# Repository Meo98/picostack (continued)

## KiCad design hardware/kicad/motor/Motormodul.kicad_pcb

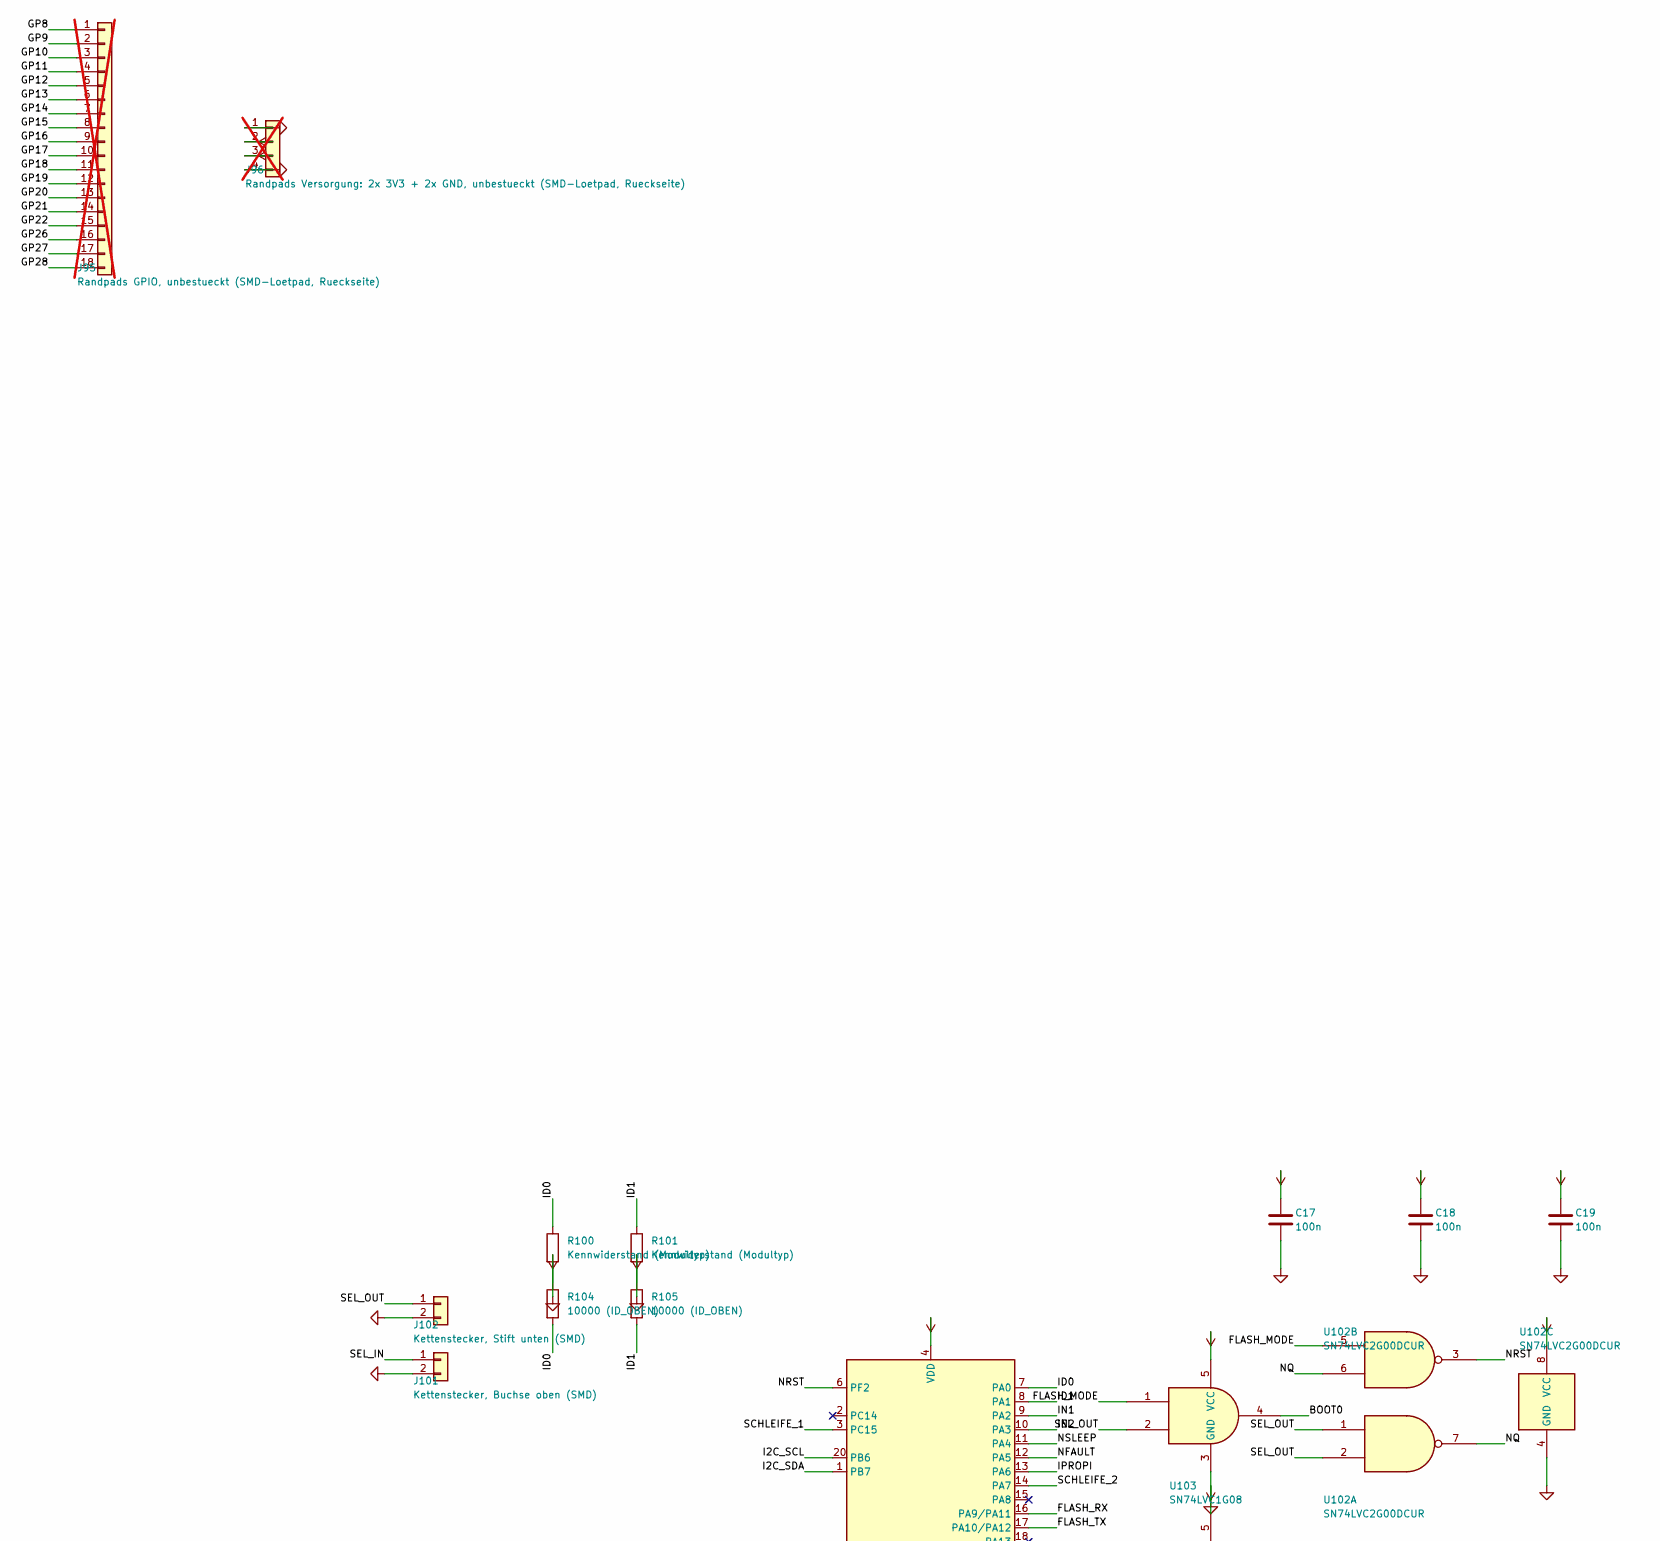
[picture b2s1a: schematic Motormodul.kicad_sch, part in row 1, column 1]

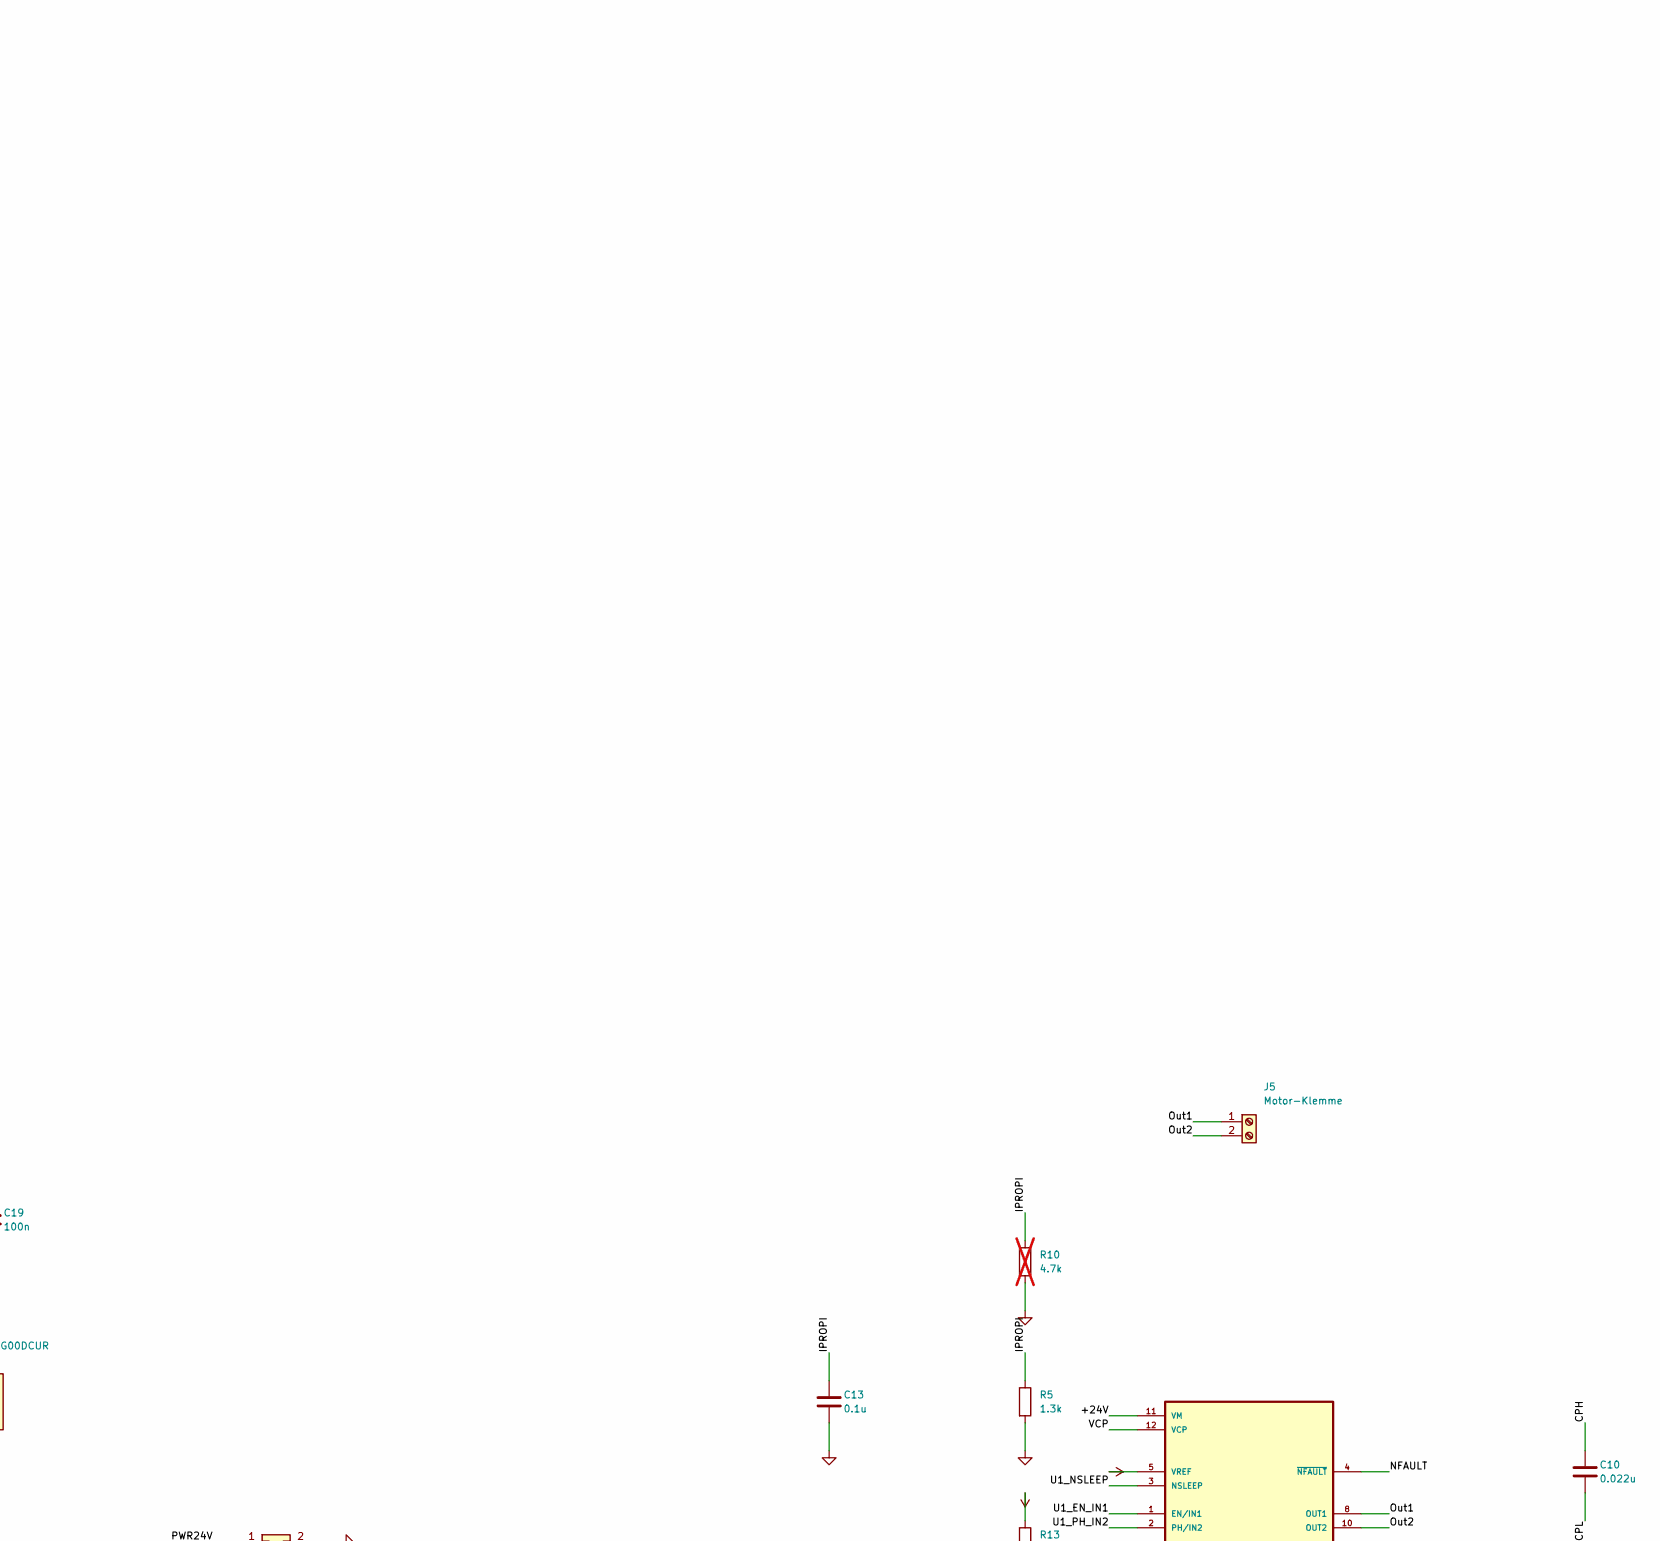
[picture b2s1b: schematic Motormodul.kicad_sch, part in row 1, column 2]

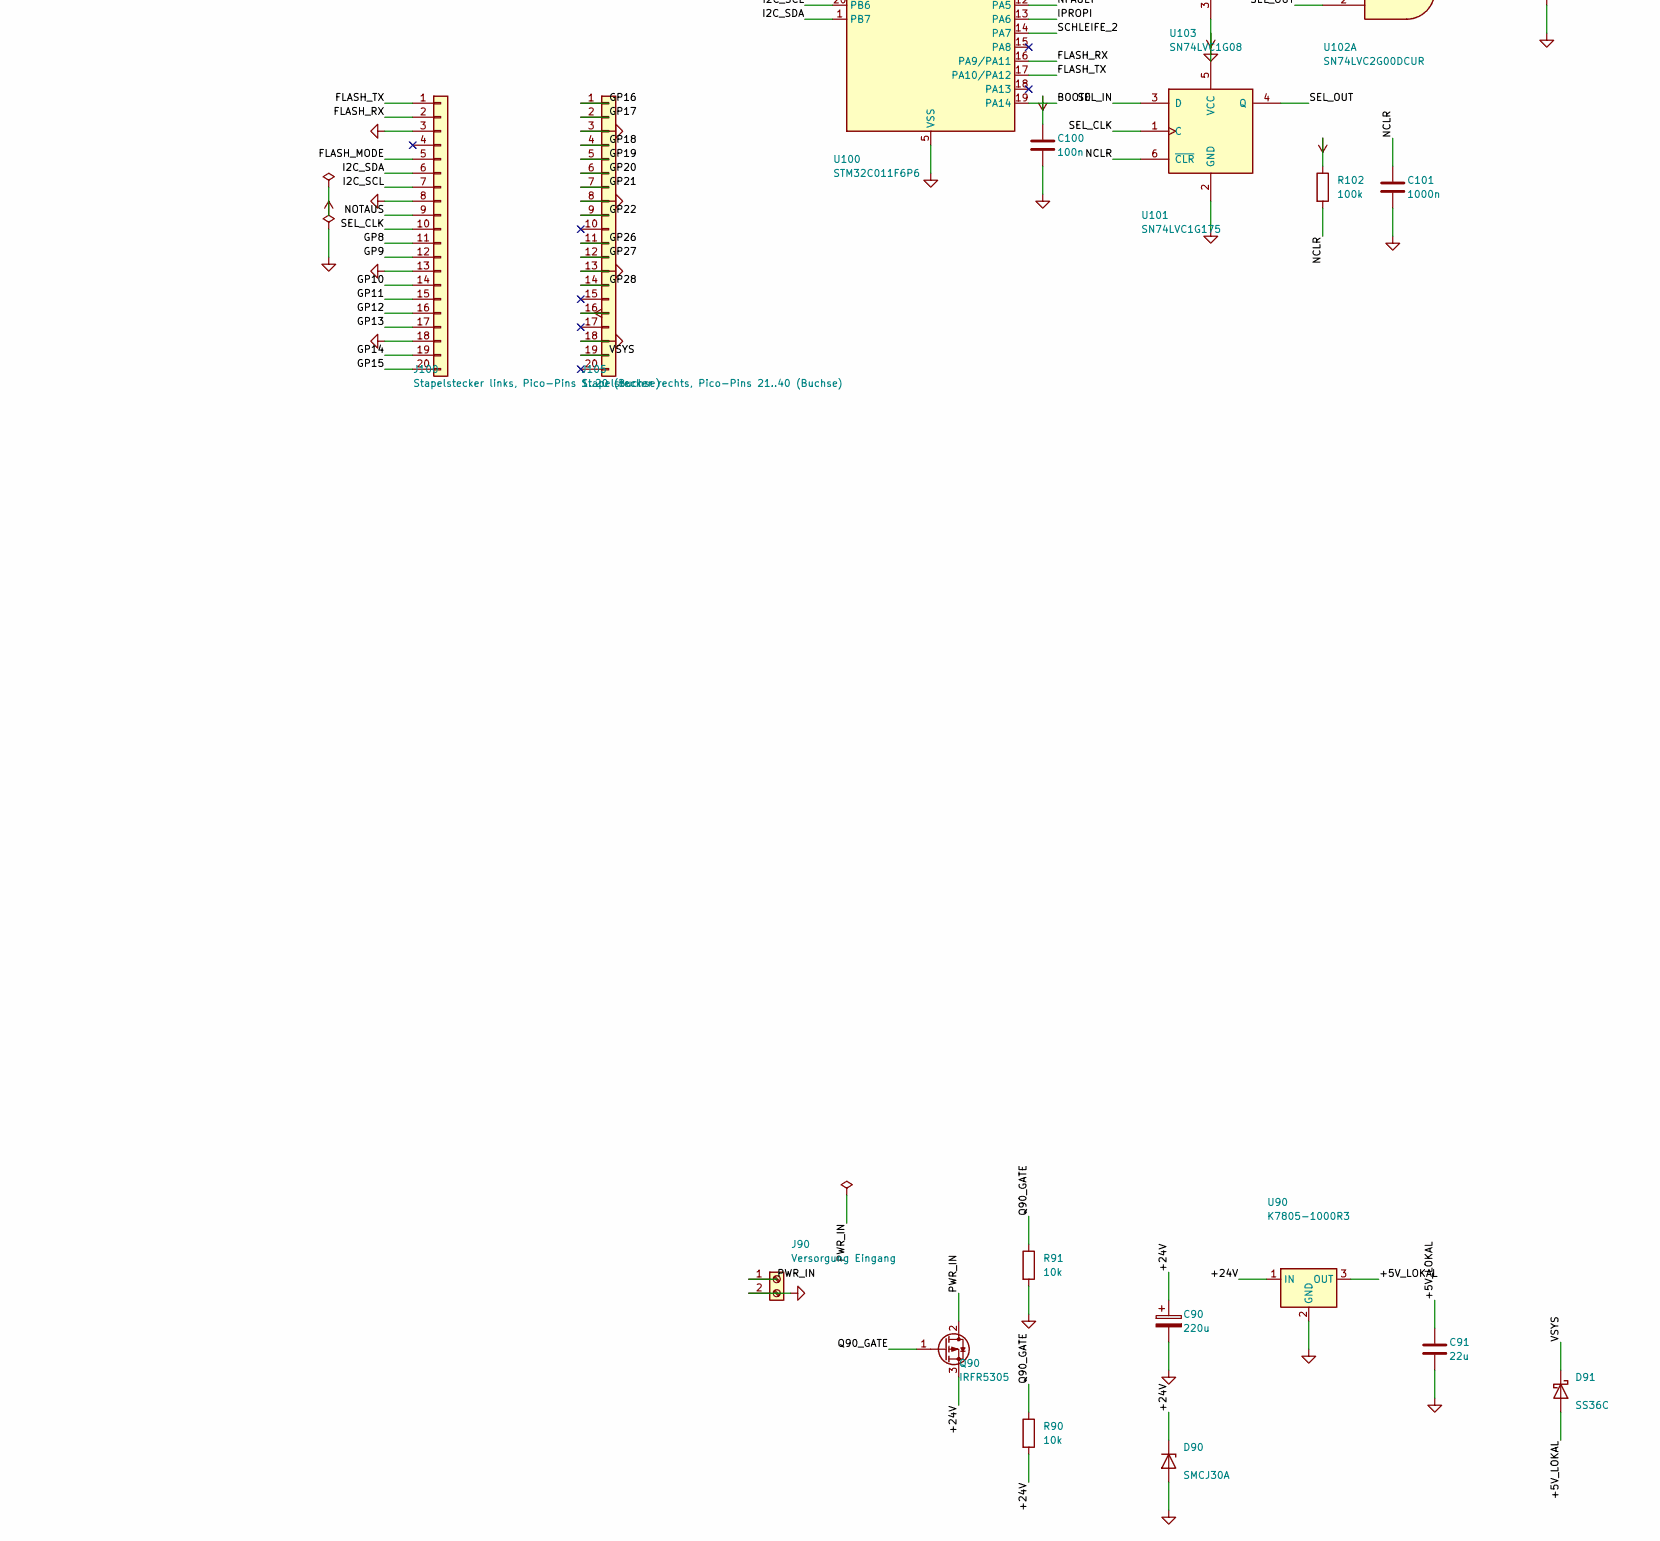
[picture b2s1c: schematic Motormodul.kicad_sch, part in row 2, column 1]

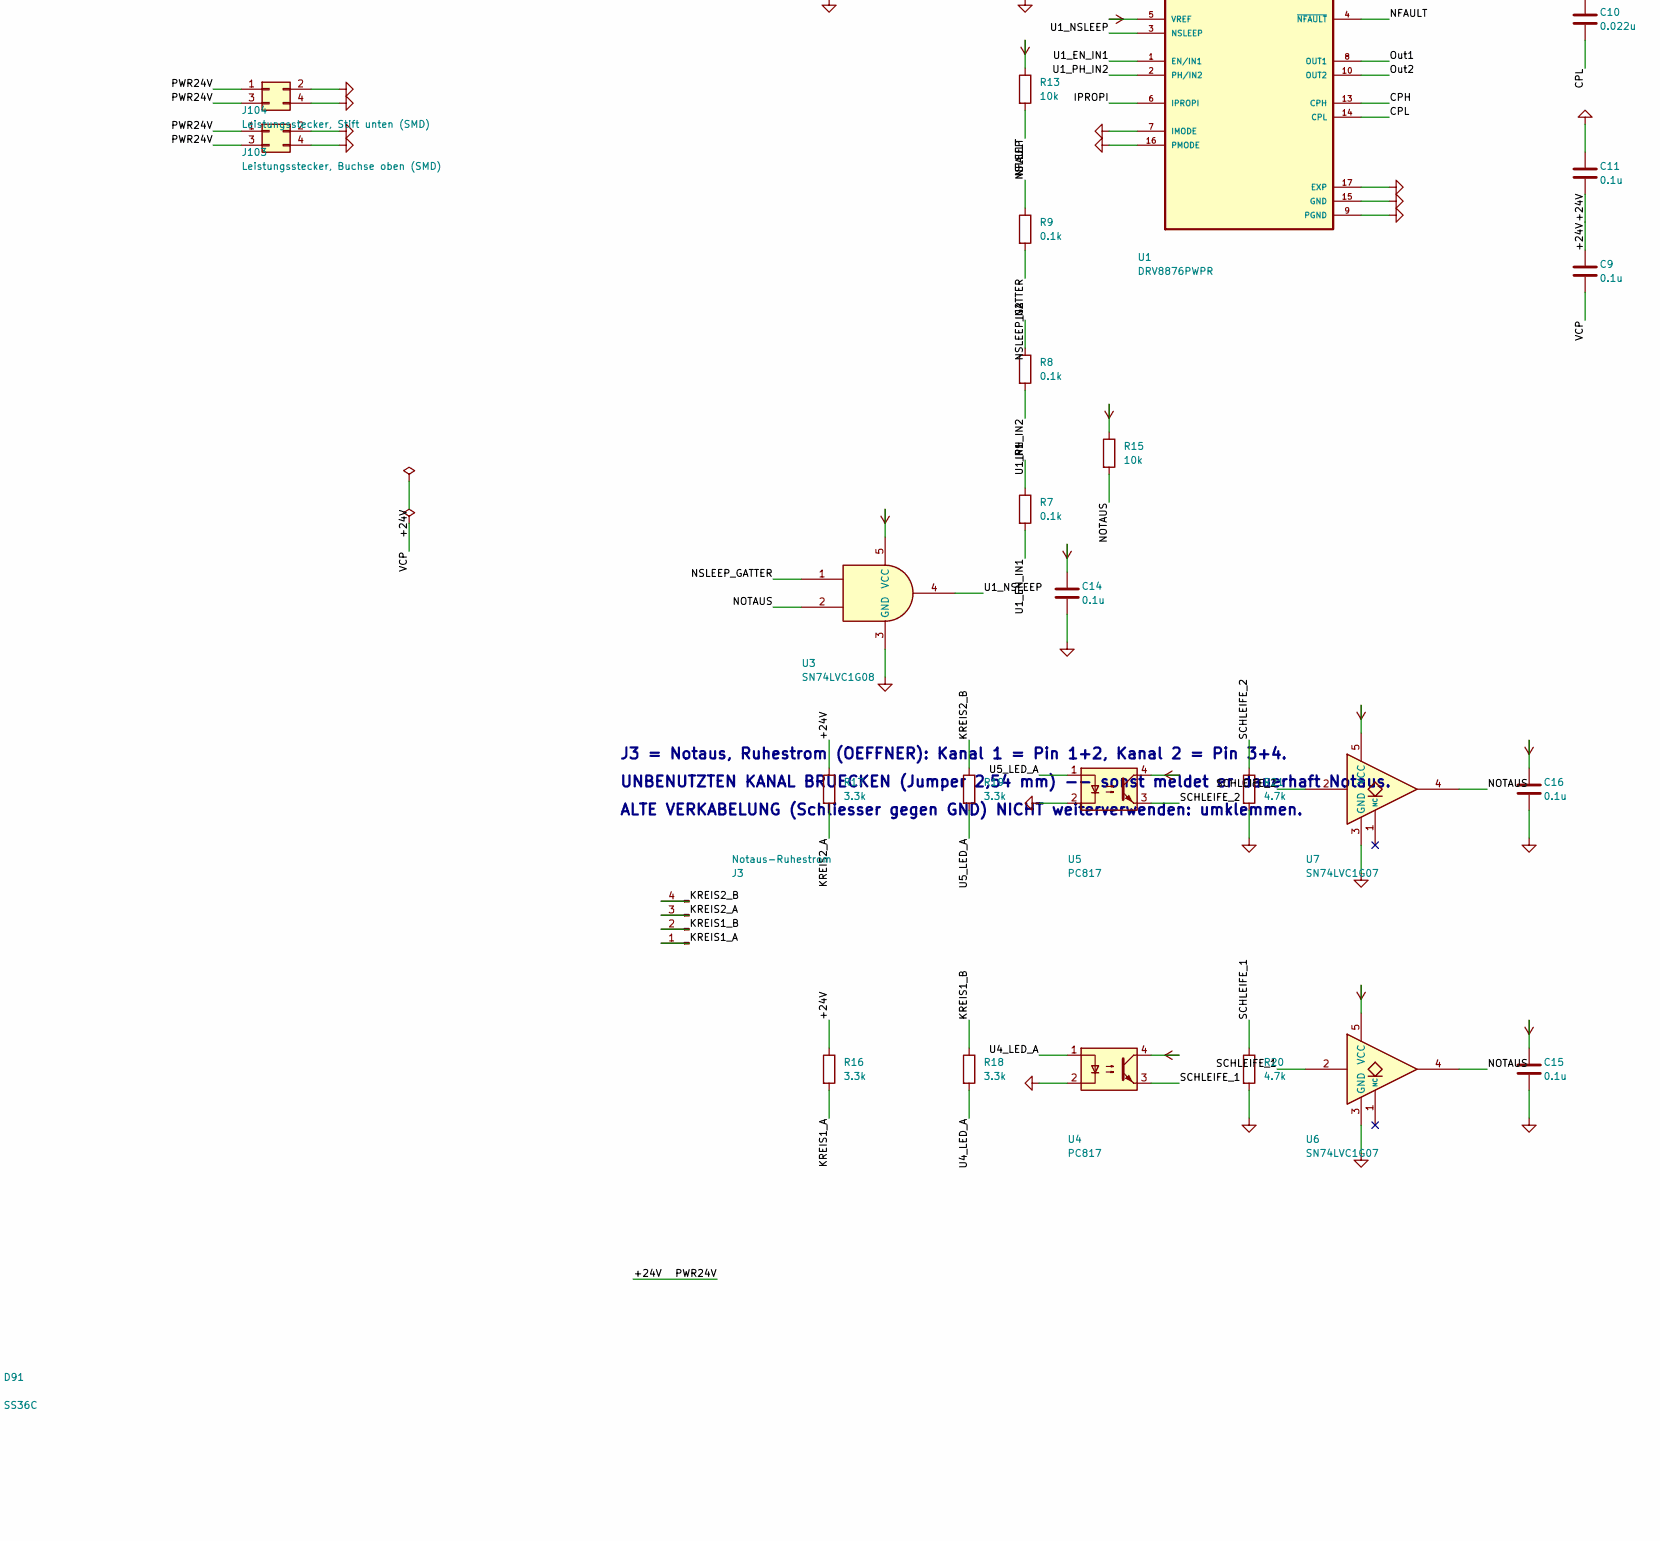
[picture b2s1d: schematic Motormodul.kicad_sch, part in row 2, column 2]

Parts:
C9, C11, C13, C14, C15, C16: 0.1u; C_0805_2012Metric_Pad1.18x1.45mm_HandSolder
C10: 0.022u; C_0805_2012Metric_Pad1.18x1.45mm_HandSolder
C17, C18, C19: 100n; C_0805_2012Metric_Pad1.18x1.45mm_HandSolder; LCSC C49678
C90: 220u; CP_Radial_D8.0mm_P3.50mm
C91: 22u; C_0805_2012Metric_Pad1.18x1.45mm_HandSolder
C100: 100n; C_0805_2012Metric_Pad1.18x1.45mm_HandSolder
C101: 1000n; C_0805_2012Metric_Pad1.18x1.45mm_HandSolder
D90: SMCJ30A; D_SMC
D91: SS36C; D_SMC
J3: Notaus-Ruhestrom; PinHeader_1x04_P2.54mm_Vertical
J5: Motor-Klemme; TerminalBlock_Phoenix_MKDS-3-2-5.08_1x02_P5.08mm_Horizontal
J90: Versorgung Eingang; TerminalBlock_Phoenix_PT-1,5-2-3.5-H_1x02_P3.50mm_Horizontal
J95: Randpads GPIO, unbestueckt (SMD-Loetpad, Ruecksei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; Randpad_Reihe_1x18; not fitted
J96: Randpads Versorgung: 2x 3V3 + 2x GND, unbestueckt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; Randpad_Reihe_1x04; not fitted
J100: Stapelstecker links, Pico-Pins 1..20 (Buchse); PinSocket_1x20_P2.54mm_Vertical
J101: Kettenstecker, Buchse oben (SMD); PinSocket_1x02_P2.54mm_Vertical_SMD_Pin1Left
J102: Kettenstecker, Stift unten (SMD); PinHeader_1x02_P2.54mm_Vertical_SMD_Pin1Left
J103: Leistungsstecker, Buchse oben (SMD); PinSocket_2x02_P2.54mm_Vertical_SMD
J104: Leistungsstecker, Stift unten (SMD); PinHeader_2x02_P2.54mm_Vertical_SMD
J105: Stapelstecker rechts, Pico-Pins 21..40 (Buchse); PinSocket_1x20_P2.54mm_Vertical
Q90: IRFR5305; TO-252-3_TabPin2
R5: 1.3k; R_0805_2012Metric_Pad1.20x1.40mm_HandSolder
R7, R8, R9: 0.1k; R_0805_2012Metric_Pad1.20x1.40mm_HandSolder
R10: 4.7k; R_0805_2012Metric_Pad1.20x1.40mm_HandSolder; not fitted
R13, R15, R90, R91: 10k; R_0805_2012Metric_Pad1.20x1.40mm_HandSolder
R16, R17, R18, R19: 3.3k; R_1206_3216Metric
R20, R21: 4.7k; R_0805_2012Metric_Pad1.20x1.40mm_HandSolder
R100, R101: Kennwiderstand (Modultyp); R_0805_2012Metric_Pad1.20x1.40mm_HandSolder
R102: 100k; R_0805_2012Metric_Pad1.20x1.40mm_HandSolder
R104, R105: 10000 (ID_OBEN); R_0805_2012Metric_Pad1.20x1.40mm_HandSolder
U1: DRV8876PWPR; IC_DRV8876PWPR
U3, U103: SN74LVC1G08; SOT-353_SC-70-5
U4, U5: PC817; PC817_SMT_Gullwing
U6, U7: SN74LVC1G07; SOT-353_SC-70-5; LCSC C7830
U90: K7805-1000R3; Converter_DCDC_RECOM_R-78B-2.0_THT
U100: STM32C011F6P6; TSSOP-20_4.4x6.5mm_P0.65mm
U101: SN74LVC1G175; SOT-363_SC-70-6
U102: SN74LVC2G00DCUR; VSSOP-8_2.3x2mm_P0.5mm

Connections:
/+5V_LOKAL: C91.1, D91.2 (A), U90.3 (OUT)
/+24V: C9.1, C11.2, C90.1, D90.1 (K), J103.1, J103.3, J104.1, J104.3, Q90.3 (S), R16.1, R17.1, R90.2, U1.11 (VM), U90.1 (IN)
/BOOT0: U100.19 (PA14), U103.4
/CPH: C10.1, U1.13 (CPH)
/CPL: C10.2, U1.14 (CPL)
/FLASH_MODE: J100.5, U102.5, U103.1
/FLASH_RX: J100.2, U100.16 (PA9/PA11)
/FLASH_TX: J100.1, U100.17 (PA10/PA12)
/GP8: J95.1, J100.11
/GP9: J95.2, J100.12
/GP10: J95.3, J100.14
/GP11: J95.4, J100.15
/GP12: J95.5, J100.16
/GP13: J95.6, J100.17
/GP14: J95.7, J100.19
/GP15: J95.8, J100.20
/GP16: J95.9, J105.1
/GP17: J95.10, J105.2
/GP18: J95.11, J105.4
/GP19: J95.12, J105.5
/GP20: J95.13, J105.6
/GP21: J95.14, J105.7
/GP22: J95.15, J105.9
/GP26: J95.16, J105.11
/GP27: J95.17, J105.12
/GP28: J95.18, J105.14
/I2C_SCL: J100.7, U100.20 (PB6)
/I2C_SDA: J100.6, U100.1 (PB7)
/ID0: R100.1, R104.2, U100.7 (PA0)
/ID1: R101.1, R105.2, U100.8 (PA1)
/IN1: R7.1, U100.9 (PA2)
/IN2: R8.1, U100.10 (PA3)
/IPROPI: C13.1, R5.1, R10.1, U1.6 (IPROPI), U100.13 (PA6)
/KREIS1_A: J3.1, R16.2
/KREIS1_B: J3.2, R18.1
/KREIS2_A: J3.3, R17.2
/KREIS2_B: J3.4, R19.1
/NCLR: C101.1, R102.2, U101.6 (~CLR)
/NFAULT: R13.2, U1.4 (~NFAULT), U100.12 (PA5)
/NOTAUS: J100.9, R15.2, U3.2, U6.4, U7.4
/NQ: U102.6, U102.7
/NRST: U100.6 (PF2), U102.3
/NSLEEP: R9.1, U100.11 (PA4)
/NSLEEP_GATTER: R9.2, U3.1
/Out1: J5.1, U1.8 (OUT1)
/Out2: J5.2, U1.10 (OUT2)
/PWR_IN: J90.1, Q90.2 (D)
/Q90_GATE: Q90.1 (G), R90.1, R91.1
/SCHLEIFE_1: R20.1, U4.3, U6.2, U100.3 (PC15)
/SCHLEIFE_2: R21.1, U5.3, U7.2, U100.14 (PA7)
/SEL_CLK: J100.10, U101.1 (C)
/SEL_IN: J101.1, U101.3 (D)
/SEL_OUT: J102.1, U101.4 (Q), U102.1, U102.2, U103.2
/U1_EN_IN1: R7.2, U1.1 (EN/IN1)
/U1_NSLEEP: U1.3 (NSLEEP), U3.4
/U1_PH_IN2: R8.2, U1.2 (PH/IN2)
/U4_LED_A: R18.2, U4.1
/U5_LED_A: R19.2, U5.1
/VCP: C9.2, U1.12 (VCP)
/VSYS: D91.1 (K), J105.19

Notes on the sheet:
J3 = Notaus, Ruhestrom (OEFFNER): Kanal 1 = Pin 1+2, Kanal 2 = Pin 3+4.
UNBENUTZTEN KANAL BRUECKEN (Jumper 2,54 mm) -- sonst meldet er dauerhaft Notaus.
ALTE VERKABELUNG (Schliesser gegen GND) NICHT weiterverwenden: umklemmen.

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
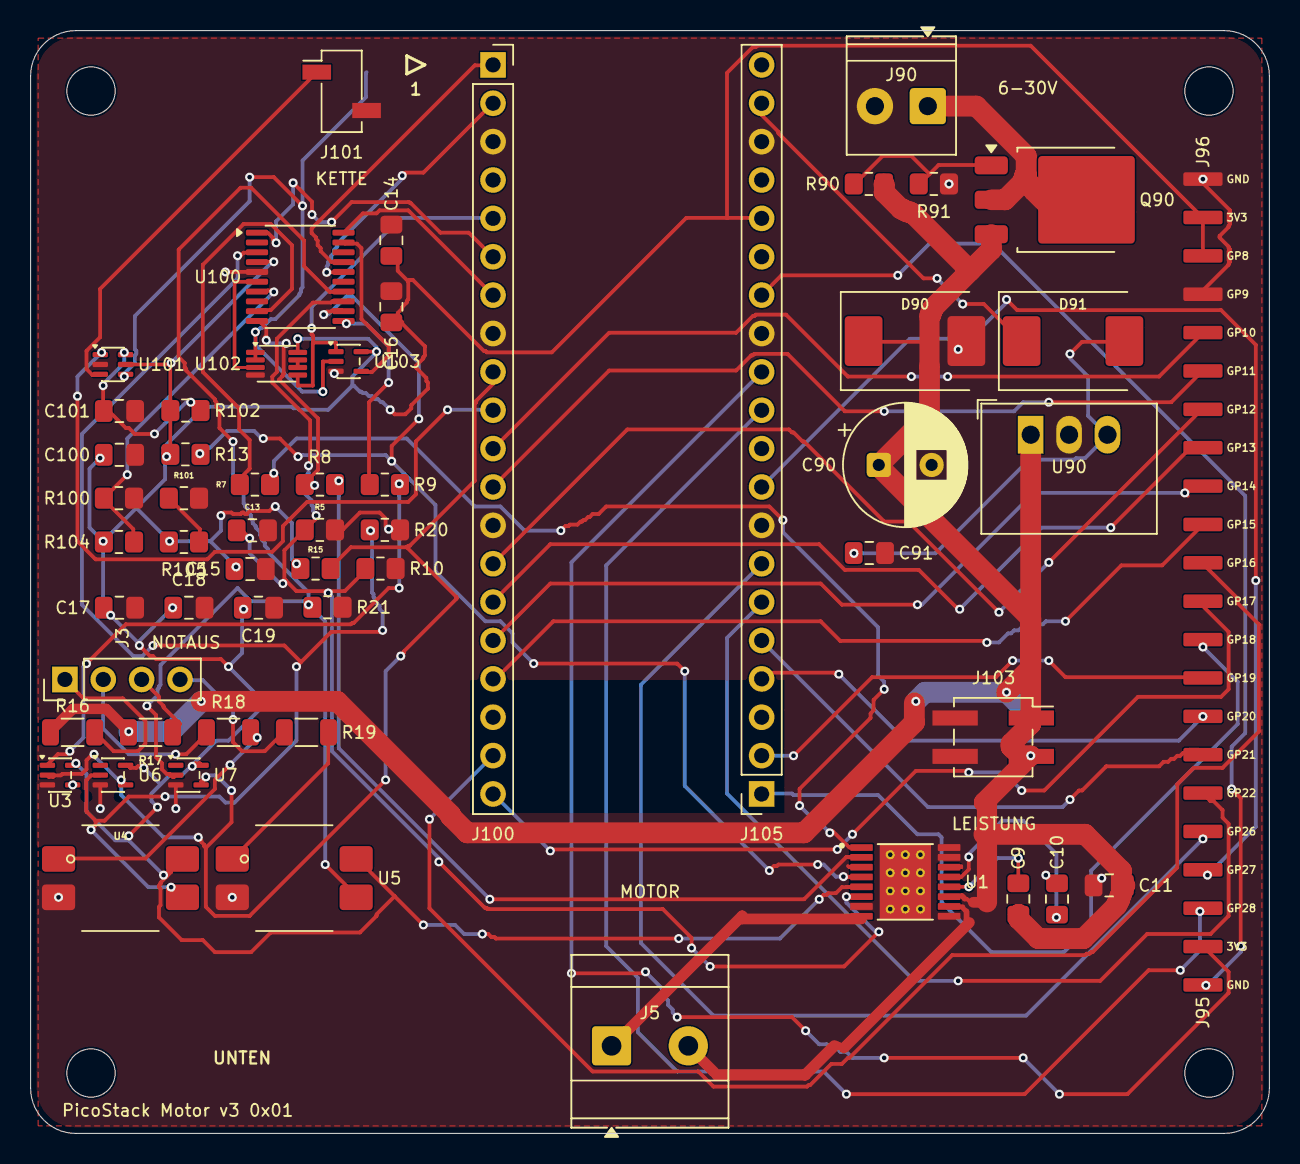
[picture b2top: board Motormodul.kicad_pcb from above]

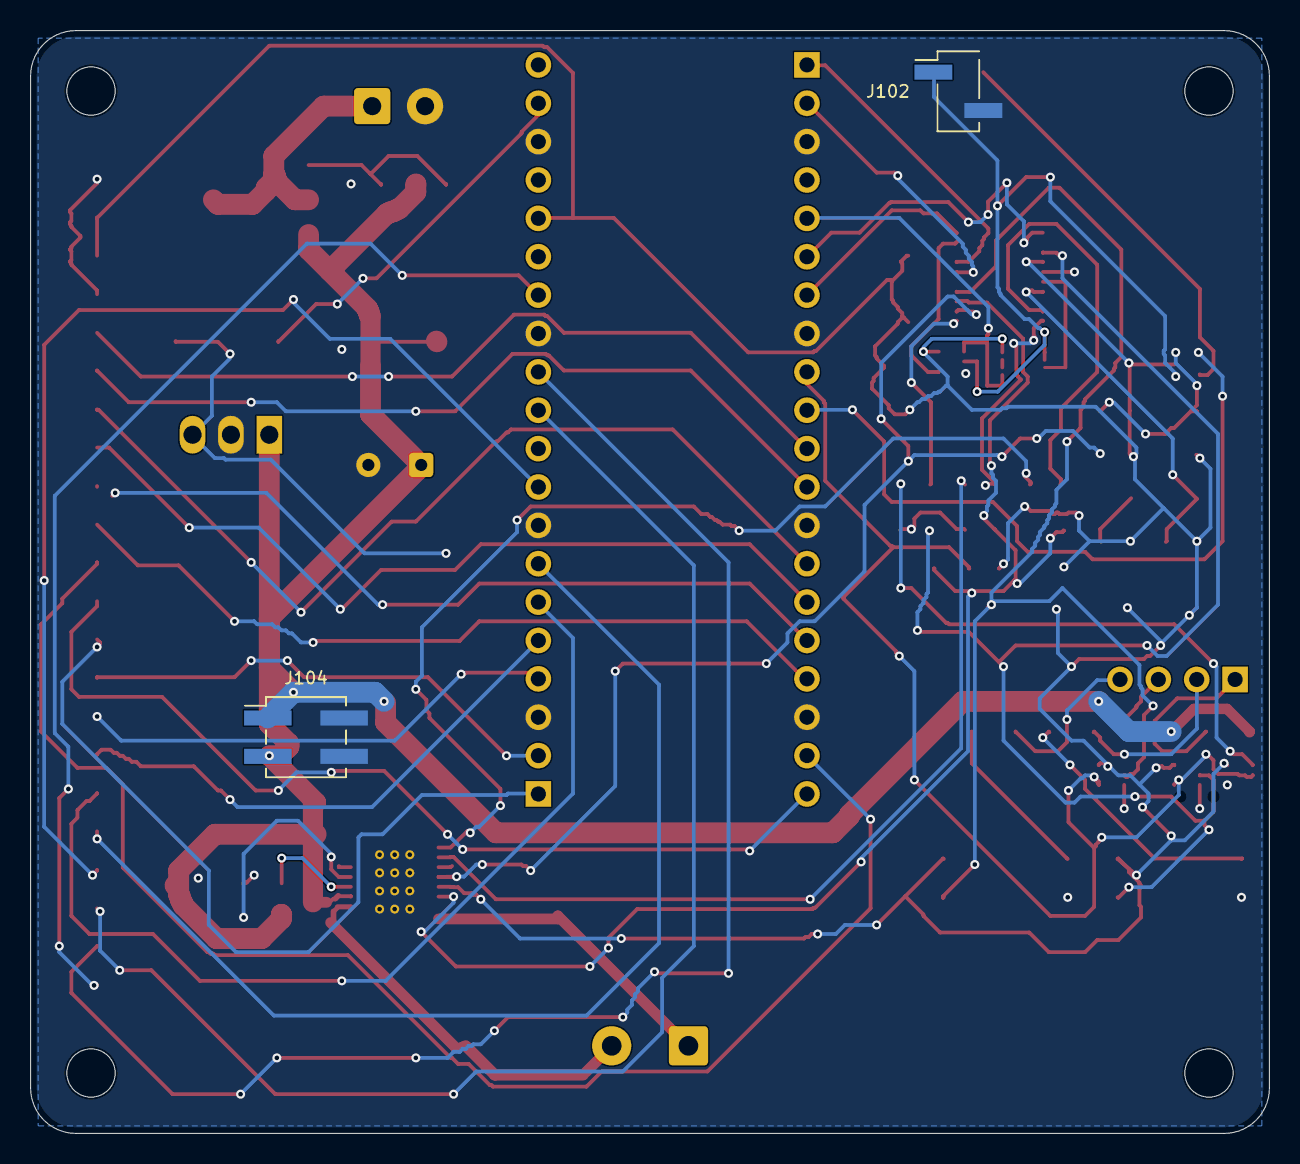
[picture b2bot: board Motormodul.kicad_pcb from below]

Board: 2 copper layers, 82.0 x 73.0 mm, 63 parts (2 on the bottom side), 62 nets.

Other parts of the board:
H1, H2, H3, H4: M3

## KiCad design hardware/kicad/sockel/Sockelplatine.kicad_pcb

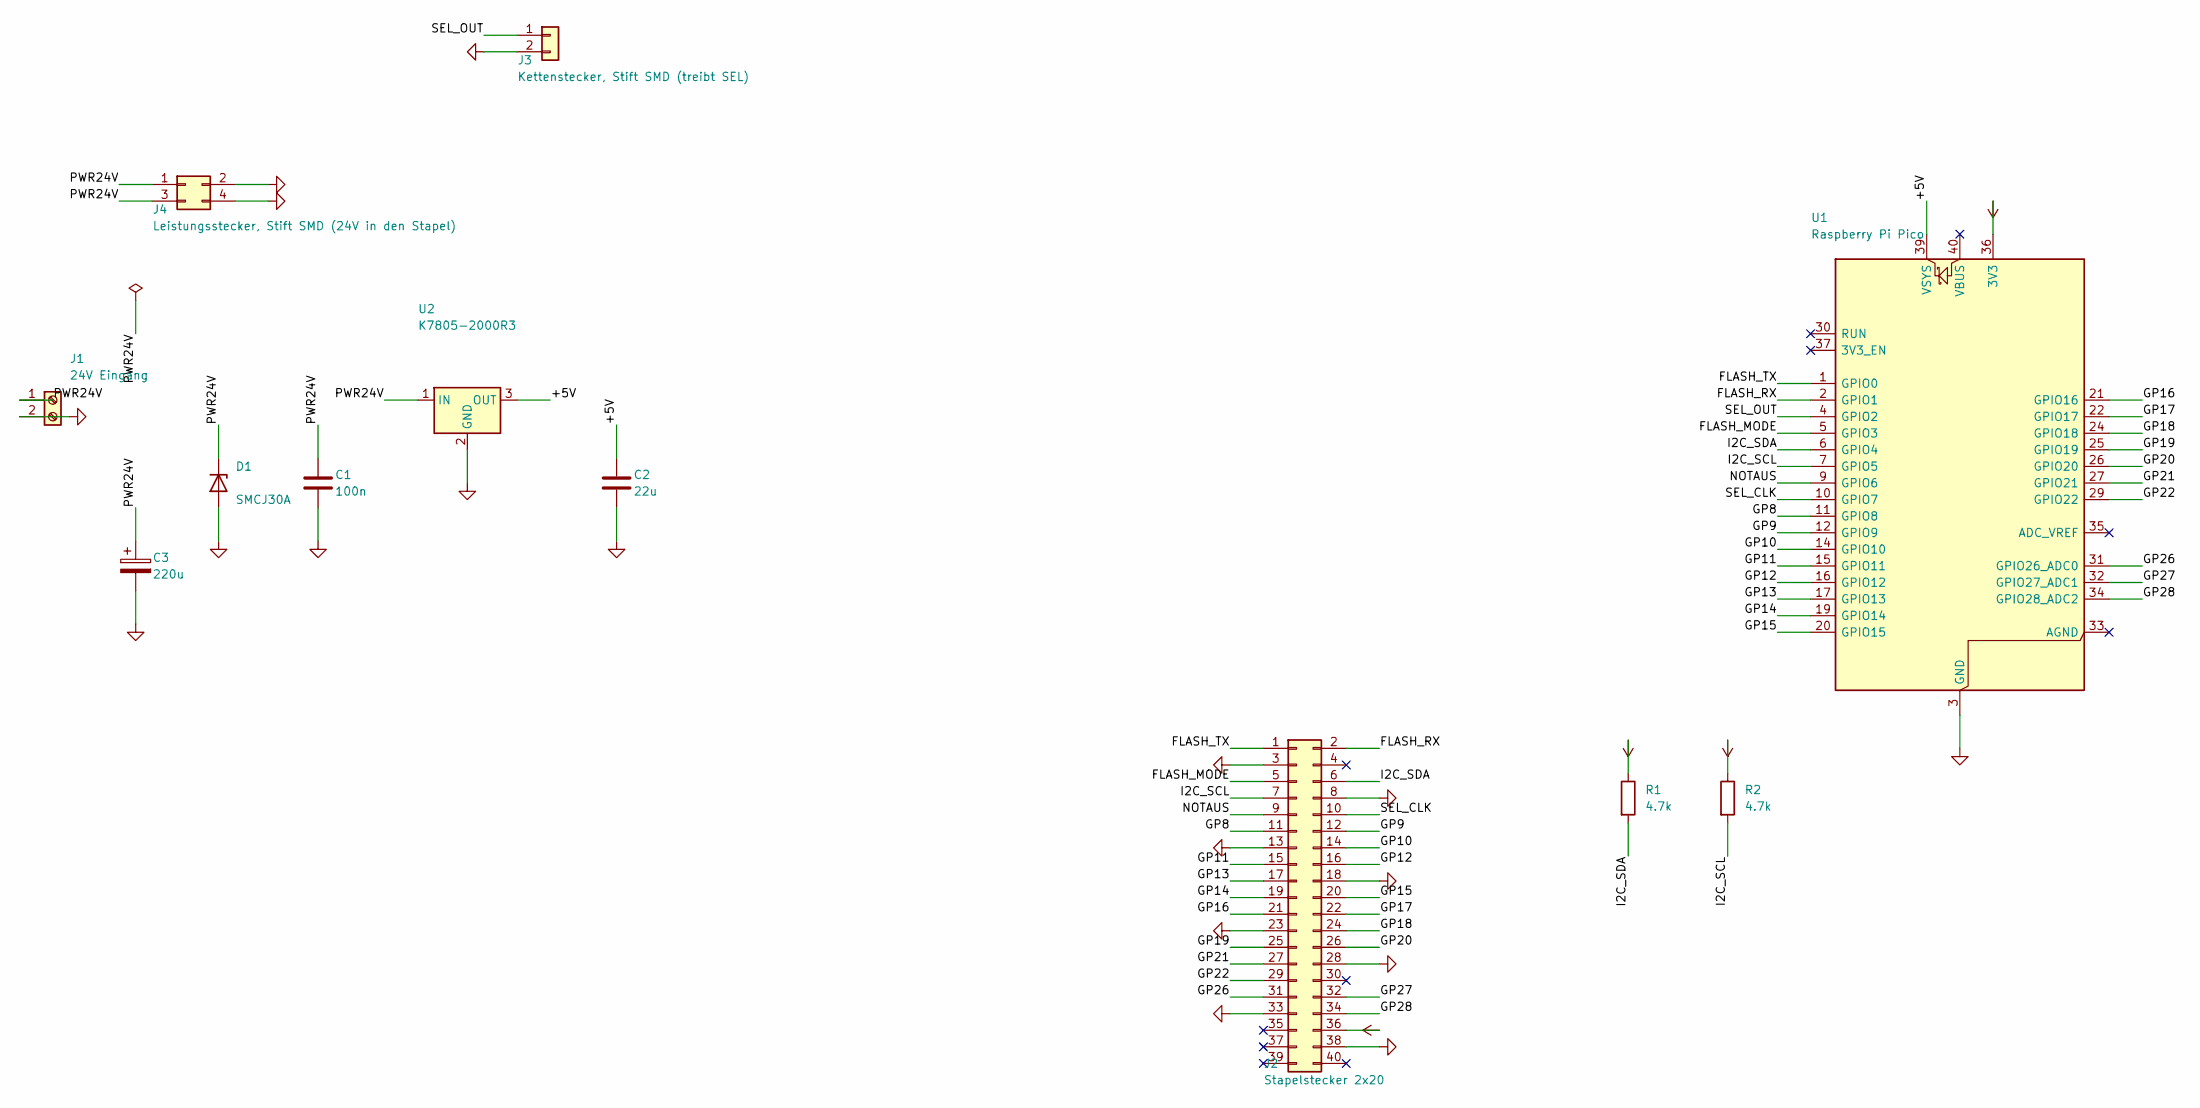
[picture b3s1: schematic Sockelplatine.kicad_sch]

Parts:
C1: 100n; C_0805_2012Metric_Pad1.18x1.45mm_HandSolder
C2: 22u; C_0805_2012Metric_Pad1.18x1.45mm_HandSolder
C3: 220u; CP_Radial_D8.0mm_P3.50mm
D1: SMCJ30A; D_SMC_Handsoldering
J1: 24V Eingang; TerminalBlock_Phoenix_MKDS-3-2-5.08_1x02_P5.08mm_Horizontal
J2: Stapelstecker 2x20; PinHeader_2x20_P2.54mm_Vertical
J3: Kettenstecker, Stift SMD (treibt SEL); PinHeader_1x02_P2.54mm_Vertical_SMD_Pin1Left
J4: Leistungsstecker, Stift SMD (24V in den Stapel); PinHeader_2x02_P2.54mm_Vertical_SMD
R1, R2: 4.7k; R_0805_2012Metric_Pad1.20x1.40mm_HandSolder
U1: Raspberry Pi Pico; RaspberryPi_Pico_Common_THT
U2: K7805-2000R3; Converter_DCDC_RECOM_R-78B-2.0_THT

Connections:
3V3: J2.36, R1.1, R2.1, U1.36 (3V3)
/+5V: C2.1, U1.39 (VSYS), U2.3 (OUT)
/FLASH_MODE: J2.5, U1.5 (GPIO3)
/FLASH_RX: J2.2, U1.2 (GPIO1)
/FLASH_TX: J2.1, U1.1 (GPIO0)
/GP8: J2.11, U1.11 (GPIO8)
/GP9: J2.12, U1.12 (GPIO9)
/GP10: J2.14, U1.14 (GPIO10)
/GP11: J2.15, U1.15 (GPIO11)
/GP12: J2.16, U1.16 (GPIO12)
/GP13: J2.17, U1.17 (GPIO13)
/GP14: J2.19, U1.19 (GPIO14)
/GP15: J2.20, U1.20 (GPIO15)
/GP16: J2.21, U1.21 (GPIO16)
/GP17: J2.22, U1.22 (GPIO17)
/GP18: J2.24, U1.24 (GPIO18)
/GP19: J2.25, U1.25 (GPIO19)
/GP20: J2.26, U1.26 (GPIO20)
/GP21: J2.27, U1.27 (GPIO21)
/GP22: J2.29, U1.29 (GPIO22)
/GP26: J2.31, U1.31 (GPIO26_ADC0)
/GP27: J2.32, U1.32 (GPIO27_ADC1)
/GP28: J2.34, U1.34 (GPIO28_ADC2)
/I2C_SCL: J2.7, R2.2, U1.7 (GPIO5)
/I2C_SDA: J2.6, R1.2, U1.6 (GPIO4)
/NOTAUS: J2.9, U1.9 (GPIO6)
/PWR24V: C1.1, C3.1, D1.1 (K), J1.1, J4.1, J4.3, U2.1 (IN)
/SEL_CLK: J2.10, U1.10 (GPIO7)
/SEL_OUT: J3.1, U1.4 (GPIO2)
GND: C1.2, C2.2, C3.2, D1.2 (A), J1.2, J2.3, J2.8, J2.13, J2.18, J2.23, J2.28, J2.33, J2.38, J3.2, J4.2, J4.4, U1.3 (GND), U1.8 (GND), U1.13 (GND), U1.18 (GND), U1.23 (GND), U1.28 (GND), U1.38 (GND), U2.2 (GND)

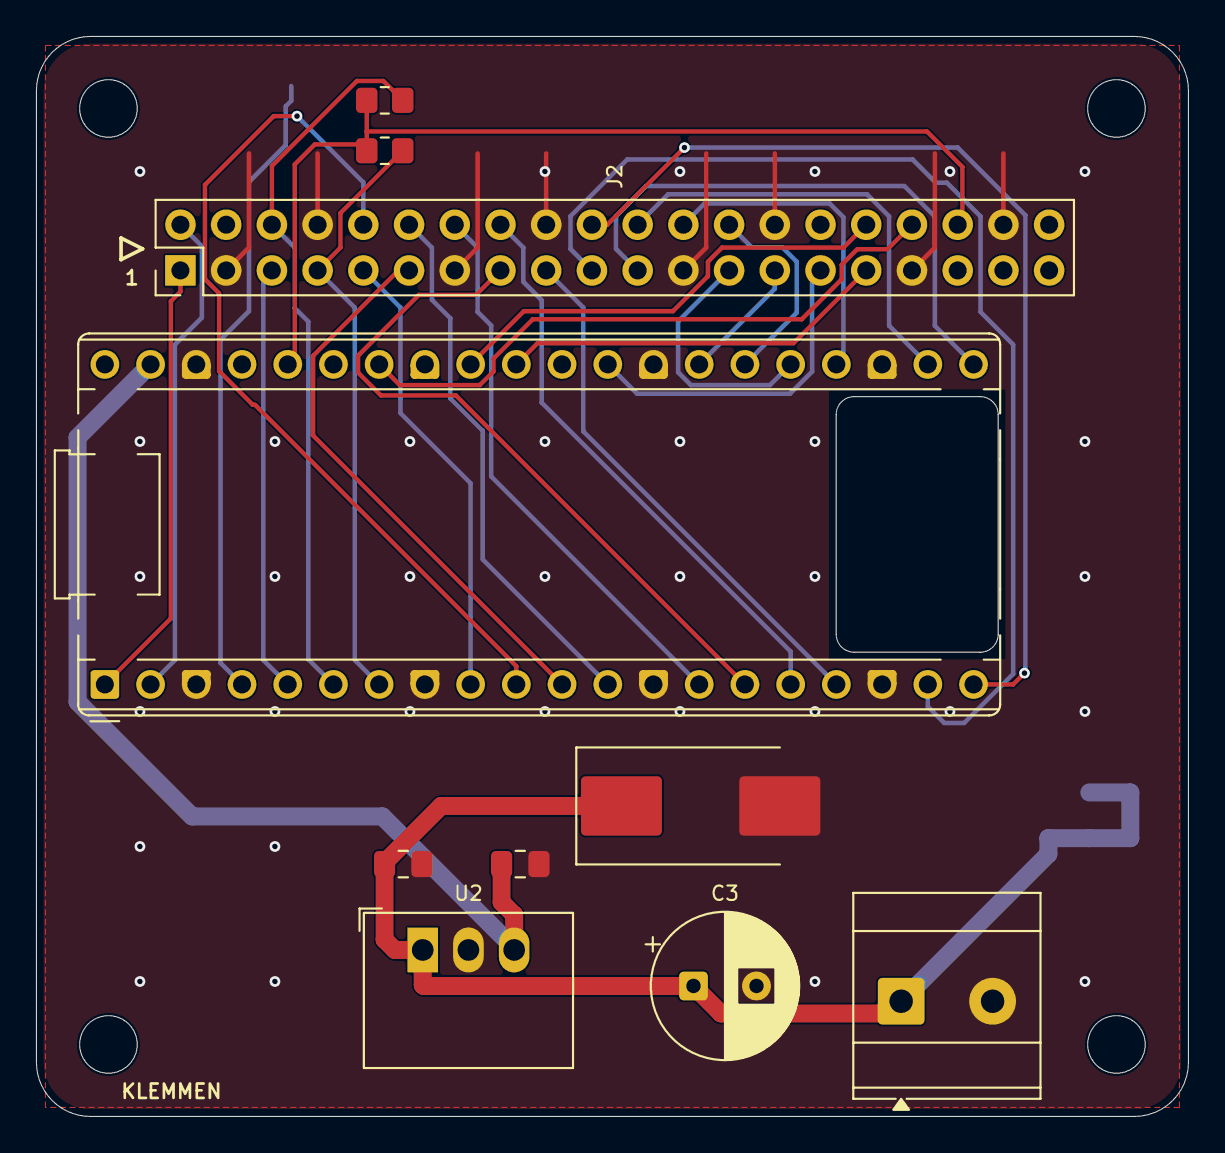
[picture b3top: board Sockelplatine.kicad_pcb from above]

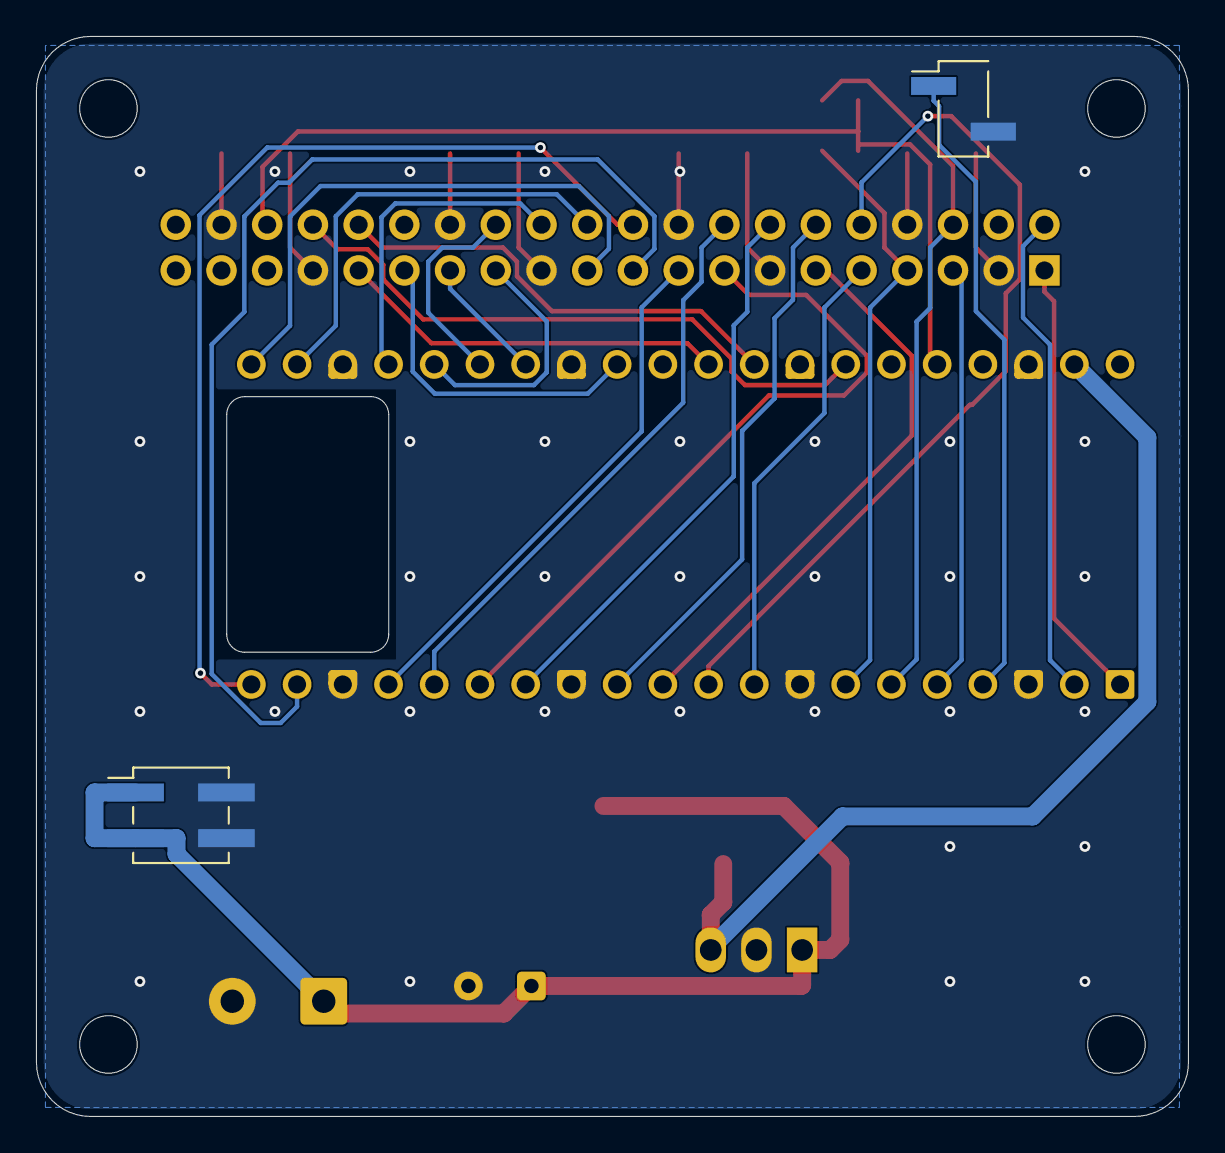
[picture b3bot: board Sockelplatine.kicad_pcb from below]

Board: 2 copper layers, 64.0 x 60.0 mm, 16 parts (2 on the bottom side), 30 nets.

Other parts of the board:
H1, H2, H3, H4: M3
